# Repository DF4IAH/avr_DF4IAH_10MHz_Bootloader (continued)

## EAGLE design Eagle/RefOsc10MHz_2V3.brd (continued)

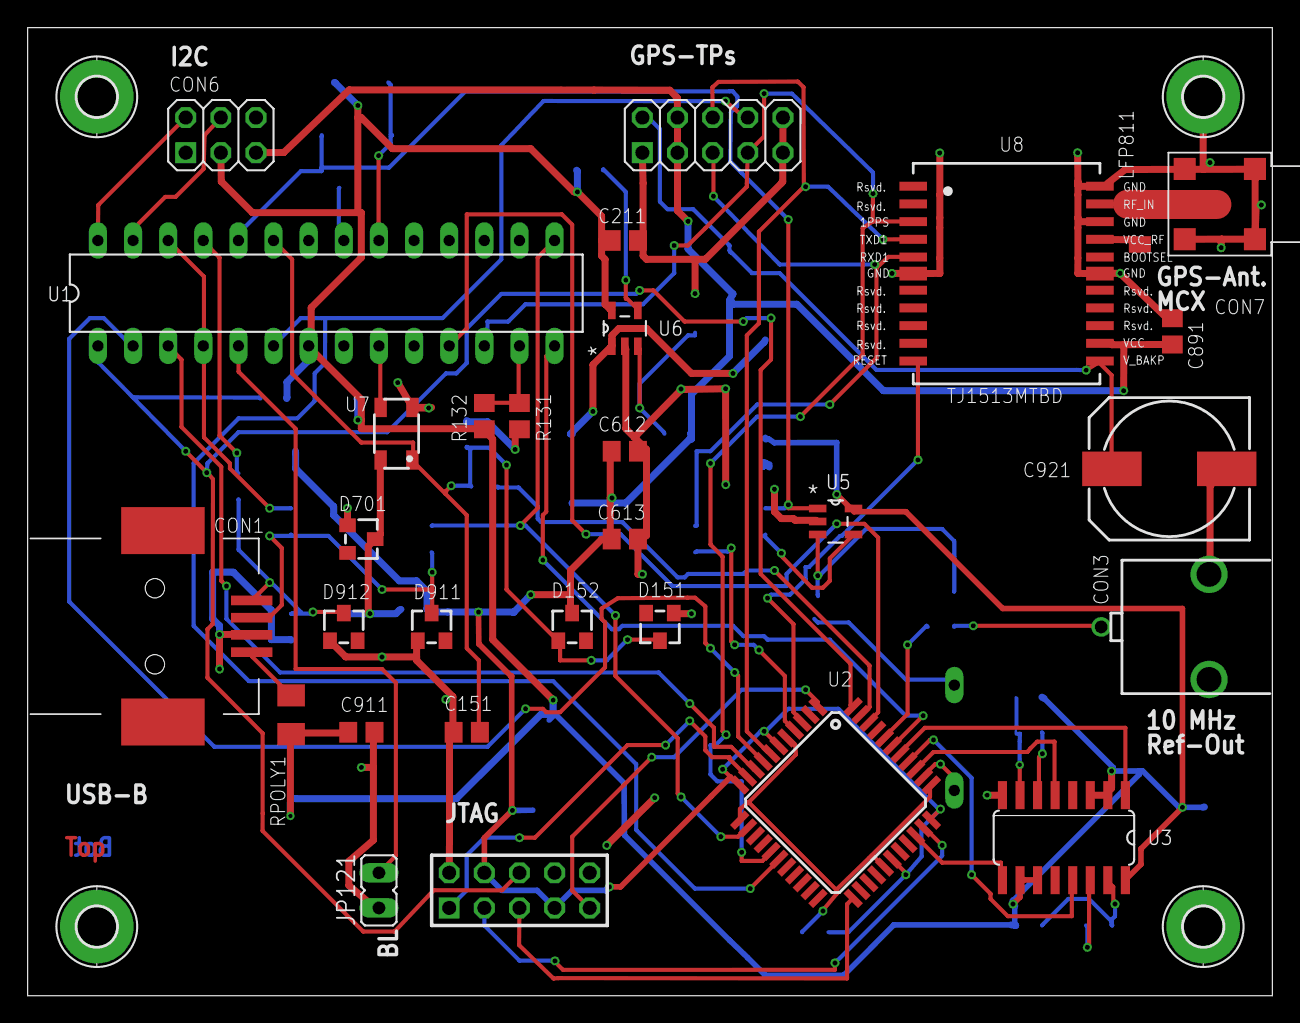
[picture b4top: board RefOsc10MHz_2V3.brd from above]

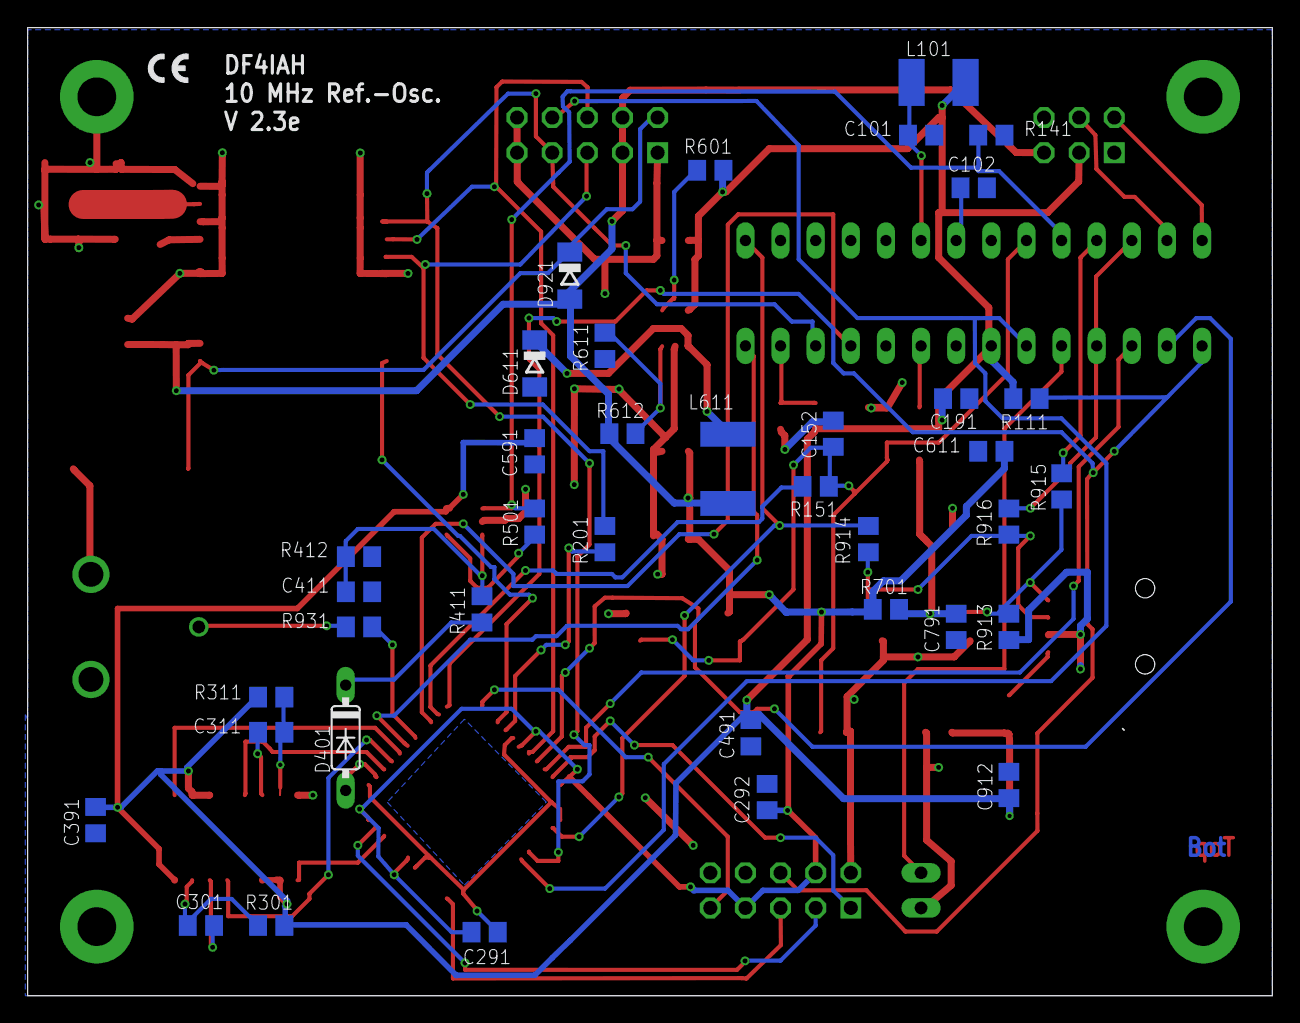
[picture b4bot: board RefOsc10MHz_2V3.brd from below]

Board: 2 copper layers, 90.0 x 70.0 mm, 72 parts (38 on the bottom side), 55 nets.

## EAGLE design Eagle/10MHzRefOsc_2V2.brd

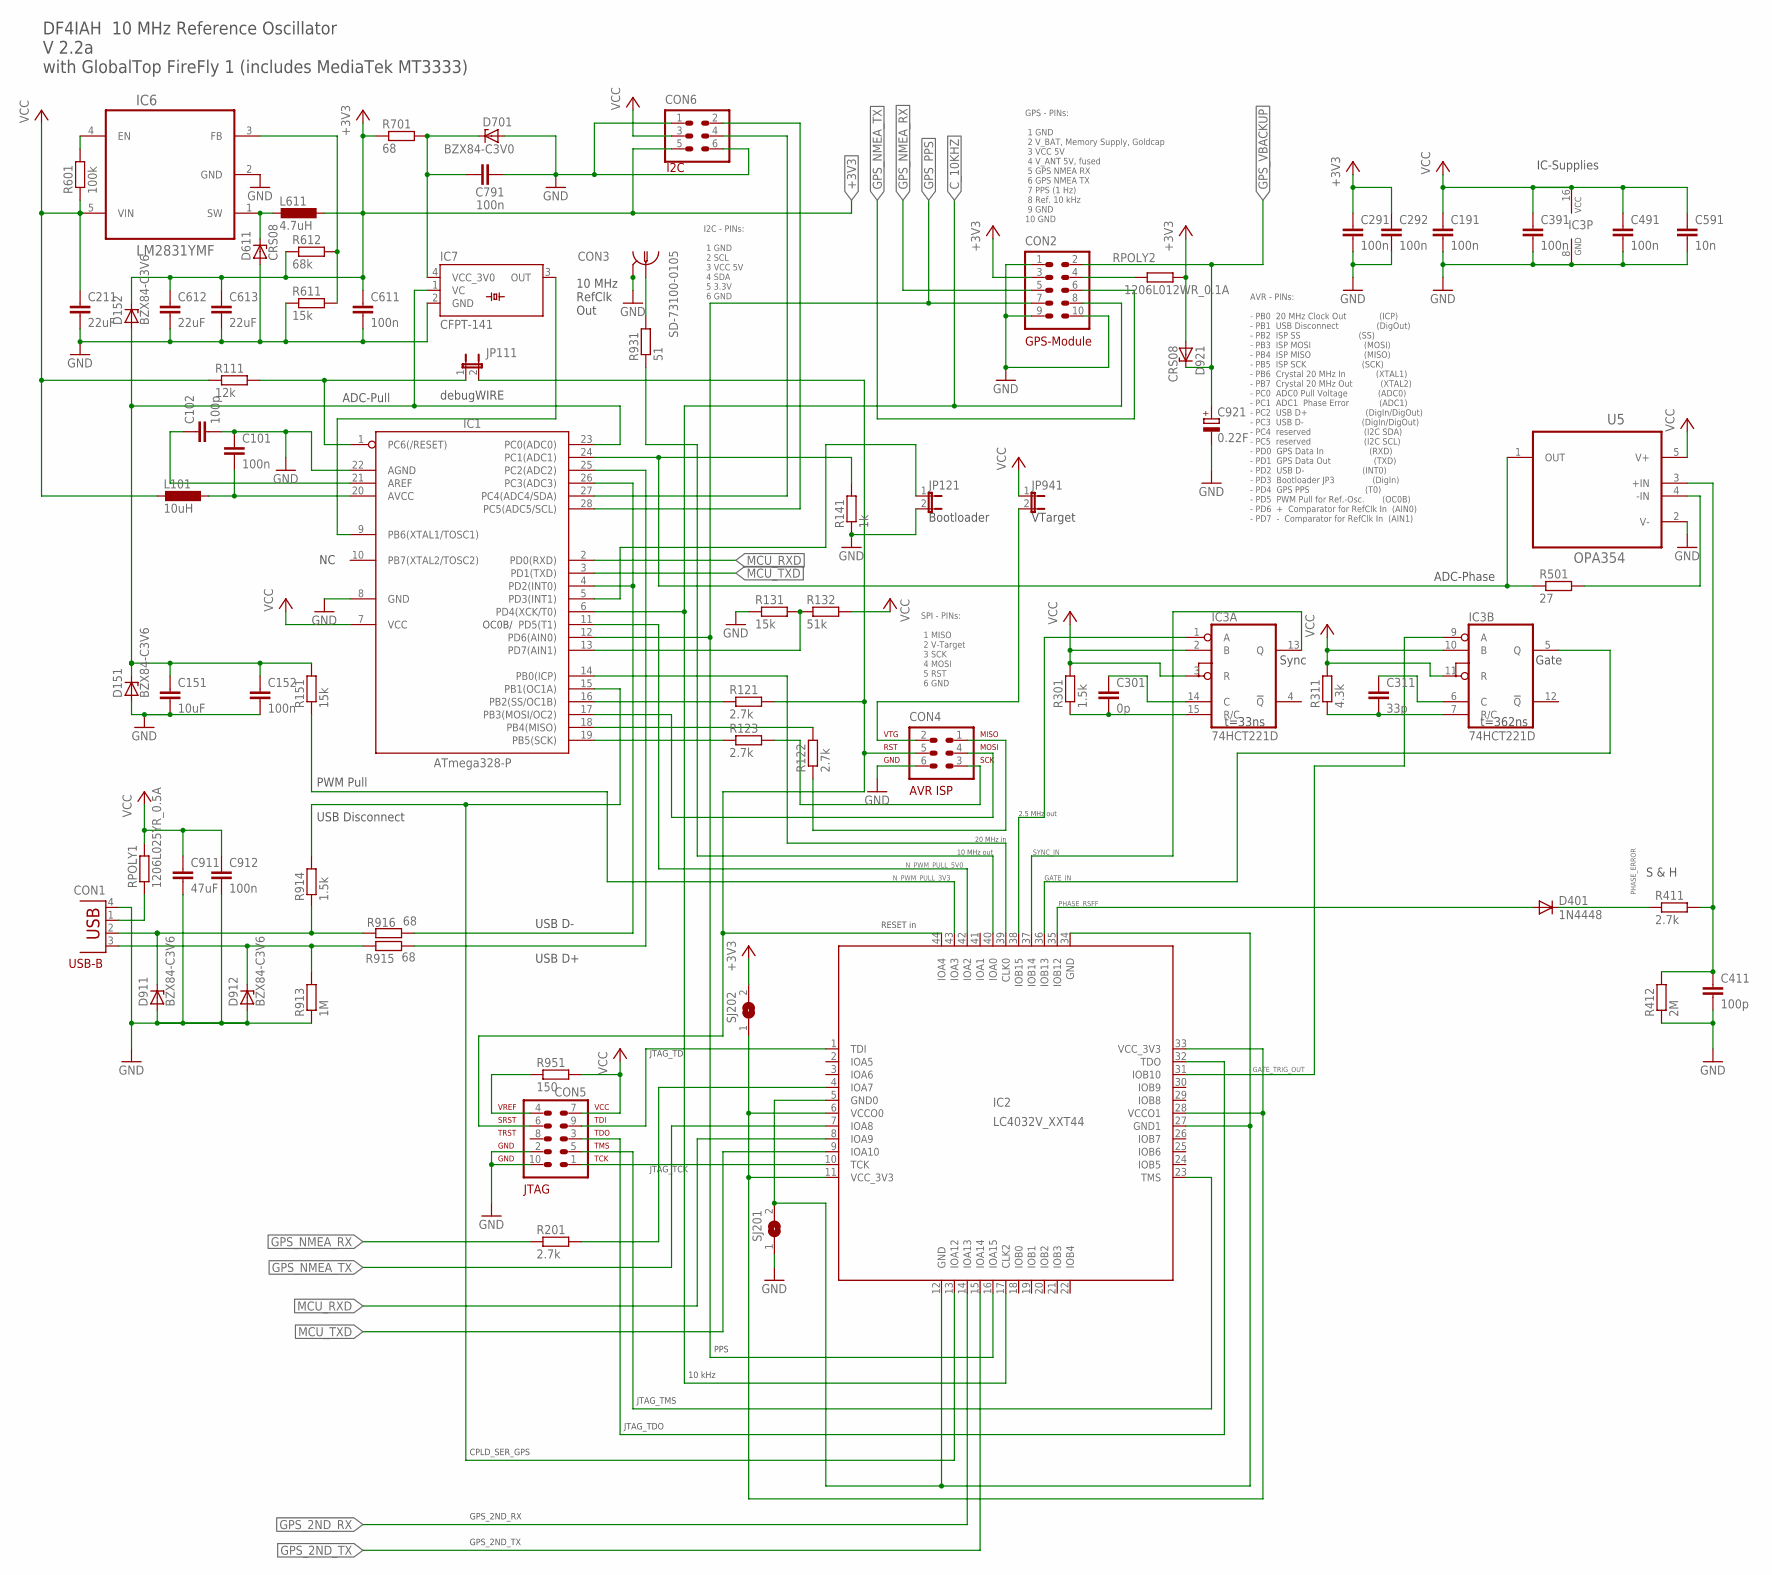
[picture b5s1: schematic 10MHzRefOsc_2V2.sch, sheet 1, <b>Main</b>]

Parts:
C101, C152, C191, C291, C292, C391, C491, C611, C791, C912: 100n; C0805
C102, C411: 100p; C0805
C151: 10uF; C0805
C211, C612, C613: 22uF; C0805
C301: 0p; C0805
C311: 33p; C0805
C591: 10n; C0805
C911: 47uF; C0805
C921: 0.22F; 140CLH-1010
CON1: TYCO-AMP_USBUSB-B_SMT; TYCO-AMP_USB-B_SMT
CON2: HEADER-2X5SMD; 2X5SMD
CON3: SD-73100-0105; MOLEX_BNC-JACK-50R_SD-73100-0105
CON4: AVR-ISP-6SMD; 2X3SMD
CON5: AVR-JTAG-10SMD; 2X5SMD
CON6: HEADER-2X3SMD; 2X03SMD
D151, D152, D911, D912: BZX84-C3V6; TO236
D401: 1N4448; SOD123
D611, D921: CRS08; SOD80C
D701: BZX84-C3V0; TO236
IC1: ATmega328-P; DIL28-3
IC2: LC4032V_XXT44; TQFP44
IC3: 74HCT221D; SO16
IC6: LM2831YMF; SOT95P280X145-5N
IC7: CFPT-141
JP111, JP121, JP941: JP1E; JP1
L101: 10uH; L1812
L611: 4.7uH; L5650M
R111: 12k; R0805
R121, R122, R123, R201, R411: 2.7k; R0805
R131, R151, R611: 15k; R0805
R132: 51k; R0805
R141: 1k; R0805
R301, R914: 1.5k; R0805
R311: 4.3k; R0805
R412: 2M; R0805
R501: 27; R0805
R601: 100k; R0805
R612: 68k; R0805
R701, R915, R916: 68; R0805
R913: 1M; R0805
R931: 51; R0805
R951: 150; R0805
RPOLY1: 1206L025YR_0.5A; M1206
RPOLY2: 1206L012WR_0.1A; M1206
SJ201, SJ202: SJ
U5: OPA354; SOT-23-5

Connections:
+3V0: C791.1, D701.C, IC7.4 (VCC_3V0), R701.2
+3V3: C291.1, C292.1, C611.1, C612.1, C613.1, CON2.3, CON6.5, D152.C, D921.A, L611.1, R612.1, R701.1, RPOLY2.2, SJ202.2
ADC_PHASE: IC1.24 (PC1(ADC1)), R141.2, R501.1, U5.1 (OUT)
ADC_PHASE_SAMPLEHOLD: C411.1, R411.2, R412.2, U5.3 (+IN)
AIN1: IC1.13 (PD7(AIN1)), R131.2, R132.1
AREF: C102.1, IC1.21 (AREF)
AVCC: C101.2, IC1.20 (AVCC), L101.1
CPLD_GPS_NMEA_RX: IC2.4 (IOA7), R201.2
C_2MHZ5: IC2.38 (IOB15), IC3.1 (A)
C_10KHZ: CON2.8, IC1.6 (PD4(XCK/T0)), IC2.17 (CLK2)
C_10MHZ: IC2.40 (IOA0), R931.1
C_20MHZ: IC1.14 (PB0(ICP)), IC2.39 (CLK0)
EN: IC6.4 (EN), R601.2
FB: IC6.3 (FB), R611.2, R612.2
GATE_IN: IC2.36 (IOB13), IC3.5 (Q)
GATE_TRIG_OUT: IC2.31 (IOB10), IC3.9 (A)
GND: C101.1, C102.2, C151.2, C152.2, C191.2, C211.2, C291.2, C292.2, C391.2, C411.2, C491.2, C591.2, C611.2, C612.2, C613.2, C791.2, C911.2, C912.2, C921.-, CON1.4 (GND), CON2.1, CON2.9, CON2.10, CON3.2, CON3.3, CON4.6, CON5.2, CON5.10, CON6.1, CON6.6, D151.A, D611.A, D701.A, D911.A, D912.A, IC1.8 (GND), IC1.22 (AGND), IC3.8 (GND), IC6.2 (GND), IC7.2 (GND), JP121.2, R131.1, R141.1, R412.1, R611.1, R913.1, SJ201.1, U5.2 (V-); also elsewhere on the board
GND_SJ1: IC2.5 (GND0), IC2.12 (GND), IC2.27 (GND1), IC2.34 (GND), SJ201.2
GPS_2ND_RX: IC2.14 (IOA13); also elsewhere on the board
GPS_2ND_TX: IC2.15 (IOA14); also elsewhere on the board
GPS_ANT_PWR: CON2.4, RPOLY2.1; also elsewhere on the board
GPS_NMEA_RX: CON2.5, R201.1; also elsewhere on the board
GPS_NMEA_TX: CON2.6, IC2.7 (IOA8); also elsewhere on the board
GPS_PPS: CON2.7, IC1.12 (PD6(AIN0)), IC2.16 (IOA15); also elsewhere on the board
GPS_VBACKUP: C921.+, CON2.2, D921.C; also elsewhere on the board
INT1: IC1.5 (PD3(INT1)), JP121.1
ISP_MISO: CON4.1, R122.1
ISP_MOSI: CON4.4, IC1.17 (PB3(MOSI/OC2))
ISP_SCK: CON4.3, R123.2
ISP_VTARGET: CON4.2, JP941.2
JTAG_SRST: CON4.5, CON5.6, IC2.44 (IOA4), JP111.2, R121.2
JTAG_TCK: CON5.1, IC2.10 (TCK)
JTAG_TDI: CON5.9, IC2.1 (TDI)
JTAG_TDO: CON5.3, IC2.32 (TDO)
JTAG_TMS: CON5.5, IC2.23 (TMS)
JTAG_VREF: CON5.4, R951.1
MCU_RXD: IC1.2 (PD0(RXD)), IC2.8 (IOA9)
MCU_TXD: IC1.3 (PD1(TXD)), IC2.9 (IOA10)
MISO: IC1.18 (PB4(MISO)), R122.2
unnamed: CON6.2, IC1.28 (PC5(ADC5/SCL))
unnamed: CON6.4, IC1.27 (PC4(ADC4/SDA))
unnamed: CON3.1, R931.2
unnamed: C311.2, IC3.7 (R/C), R311.1
unnamed: C311.1, IC3.6 (C)
unnamed: C301.2, IC3.15 (R/C), R301.1
unnamed: C301.1, IC3.14 (C)
N_ADC_PULL: C151.1, C152.1, D151.C, D152.A, IC1.23 (PC0(ADC0)), IC7.1 (VC), R151.2
N_PWM_PULL_3V3: IC2.43 (IOA3), R151.1
N_PWM_PULL_5V0: IC1.11 (PD5(T1)), IC2.42 (IOA2)
N_USB_DISC: IC1.15 (PB1(OC1A)), IC2.13 (IOA12), R914.2
N_USB_DMNS: IC1.4 (PD2(INT0)), IC1.26 (PC3(ADC3)), R916.2
N_USB_DPLS: IC1.25 (PC2(ADC2)), R915.2
PHASE_ERROR: D401.C, R411.1
PHASE_RSFF: D401.A, IC2.35 (IOB12)
RESET: IC1.1 (PC6(/RESET)), JP111.1, R111.2
SCK: IC1.19 (PB5(SCK)), R123.1
SS: IC1.16 (PB2(SS/OC1B)), R121.1
SW: D611.C, IC6.1 (SW), L611.2
SYNC_IN: IC2.37 (IOB14), IC3.13 (Q)
TOSC1: IC1.9 (PB6(XTAL1/TOSC1)), IC7.3 (OUT)
U5_FB: R501.2, U5.4 (-IN)
USB_D_MIN: CON1.2 (D-), D911.C, R914.1, R916.1
USB_D_PLS: CON1.3 (D+), D912.C, R913.2, R915.1
USB_PWR: CON1.1 (VBUS), RPOLY1.1
VCC: C191.1, C211.1, C391.1, C491.1, C591.1, C911.1, C912.1, CON5.7, CON6.3, IC1.7 (VCC), IC3.2 (B), IC3.3 (R), IC3.10 (B), IC3.11 (R), IC3.16 (VCC), IC6.5 (VIN), JP941.1, L101.2, R111.1, R132.2, R301.2, R311.2, R601.1, R951.2, RPOLY1.2, U5.5 (V+)
VCC_3V3_SJ2: IC2.6 (VCCO0), IC2.11 (VCC_3V3), IC2.28 (VCCO1), IC2.33 (VCC_3V3), SJ202.1

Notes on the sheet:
VTarget
debugWIRE
USB-B
AVR - PINs: - PB0 20 MHz Clock Out (ICP) - PB1 USB Disconnect (DigOut) - PB2 ISP SS (SS) - PB3 ISP MOSI (MOSI) - PB4 ISP MISO (MISO) - PB5 ISP SCK (SCK) - PB6 Crystal 20 MHz In (XTAL1) - PB7 Crystal 20 MHz Out (XTAL2) - PC0 ADC0 Pull Voltage (ADC0) - PC1 ADC1 Phase Error (ADC1) - PC2 USB D+ (DigIn/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
10 MHz RefClk Out
Bootloader
Gate
GPS-Module
GPS - PINs: 1 GND 2 V_BAT, Memory Supply, Goldcap 3 VCC 5V 4 V_ANT 5V, fused 5 GPS NMEA RX 6 GPS NMEA TX 7 PPS (1 Hz) 8 Ref. 10 kHz 9 GND 10 GND
S & H
ADC-Phase
PWM Pull
ADC-Pull
Sync
t=33ns
t=362ns
IC-Supplies
20 MHz in
10 MHz out
2.5 MHz out
DF4IAH 10 MHz Reference Oscillator V 2.2a with GlobalTop FireFly 1 (includes MediaTek MT3333)
USB Disconnect
USB D-
USB D+
SPI - PINs: 1 MISO 2 V-Target 3 SCK 4 MOSI 5 RST 6 GND
10 kHz
PPS
RESET in
JTAG_TMS
JTAG_TDO
JTAG_TCK
JTAG_TDI
CPLD_SER_GPS
I2C - PINs: 1 GND 2 SCL 3 VCC 5V 4 SDA 5 3.3V 6 GND
I2C
OC0B/
GPS_2ND_RX
GPS_2ND_TX

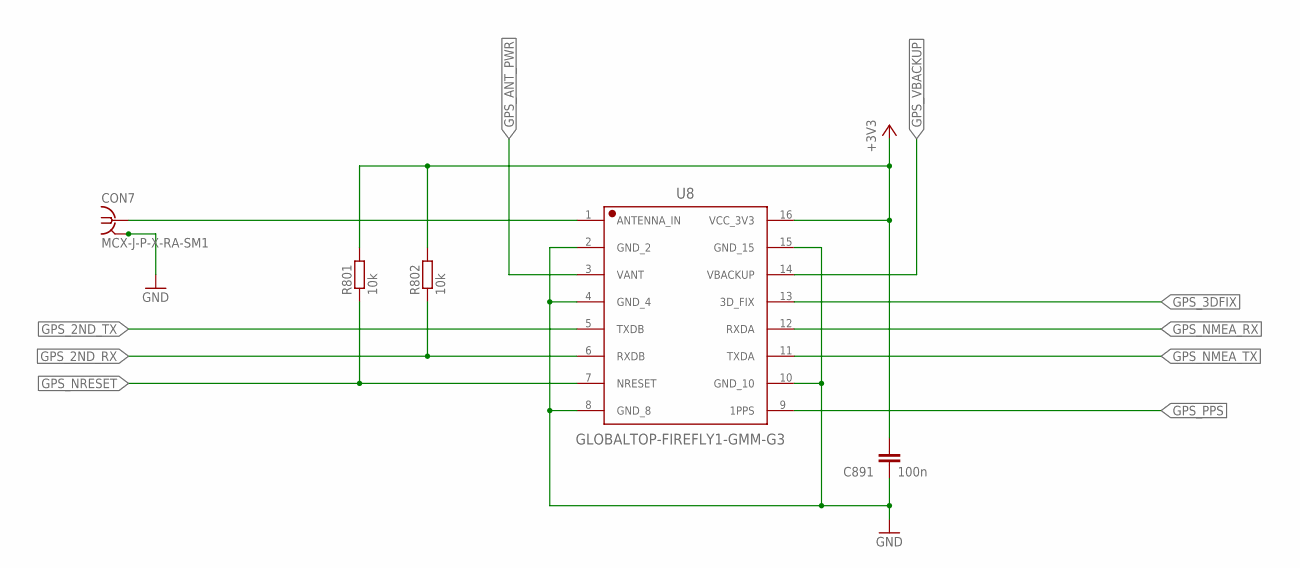
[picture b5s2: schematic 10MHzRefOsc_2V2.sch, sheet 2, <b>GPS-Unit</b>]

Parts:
C891: 100n; C0805
CON7: MCX-J-P-X-RA-SM1
R801, R802: 10k; R0805
U8: GLOBALTOP-FIREFLY1-GMM-G3

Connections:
GND: C891.2, CON7.2, CON7.3, CON7.4, CON7.5, U8.2 (GND_2), U8.4 (GND_4), U8.8 (GND_8), U8.10 (GND_10), U8.15 (GND_15); also elsewhere on the board
GPS_2ND_RX: R802.1, U8.6 (RXDB); also elsewhere on the board
GPS_2ND_TX: U8.5 (TXDB); also elsewhere on the board
GPS_3DFIX: U8.13 (3D_FIX)
GPS_ANT_PWR: U8.3 (VANT); also elsewhere on the board
GPS_NMEA_RX: U8.12 (RXDA); also elsewhere on the board
GPS_NMEA_TX: U8.11 (TXDA); also elsewhere on the board
GPS_NRESET: R801.1, U8.7 (NRESET)
GPS_PPS: U8.9 (1PPS); also elsewhere on the board
GPS_VBACKUP: U8.14 (VBACKUP); also elsewhere on the board
unnamed: CON7.1, U8.1 (ANTENNA_IN)
VCC_3V3: C891.1, R801.2, R802.2, U8.16 (VCC_3V3)

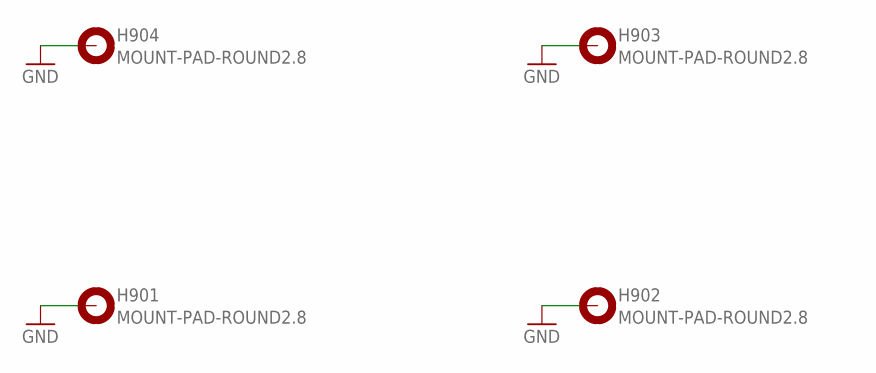
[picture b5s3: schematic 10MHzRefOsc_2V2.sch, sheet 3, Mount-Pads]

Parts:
H901, H902, H903, H904: MOUNT-PAD-ROUND2.8; 2,8-PAD

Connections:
GND: H901.B2,8, H902.B2,8, H903.B2,8, H904.B2,8; also elsewhere on the board

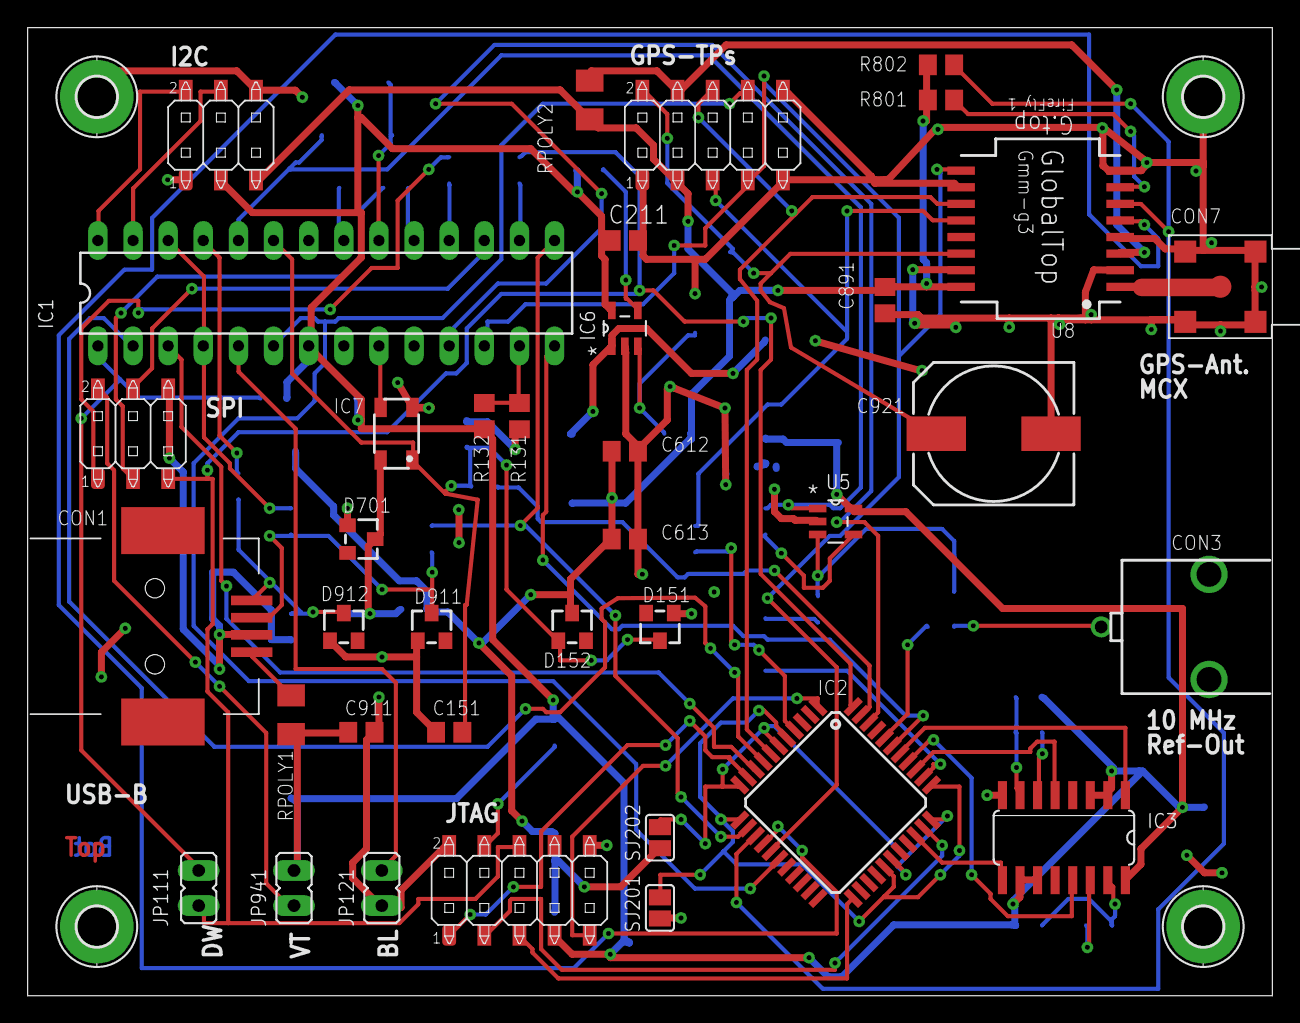
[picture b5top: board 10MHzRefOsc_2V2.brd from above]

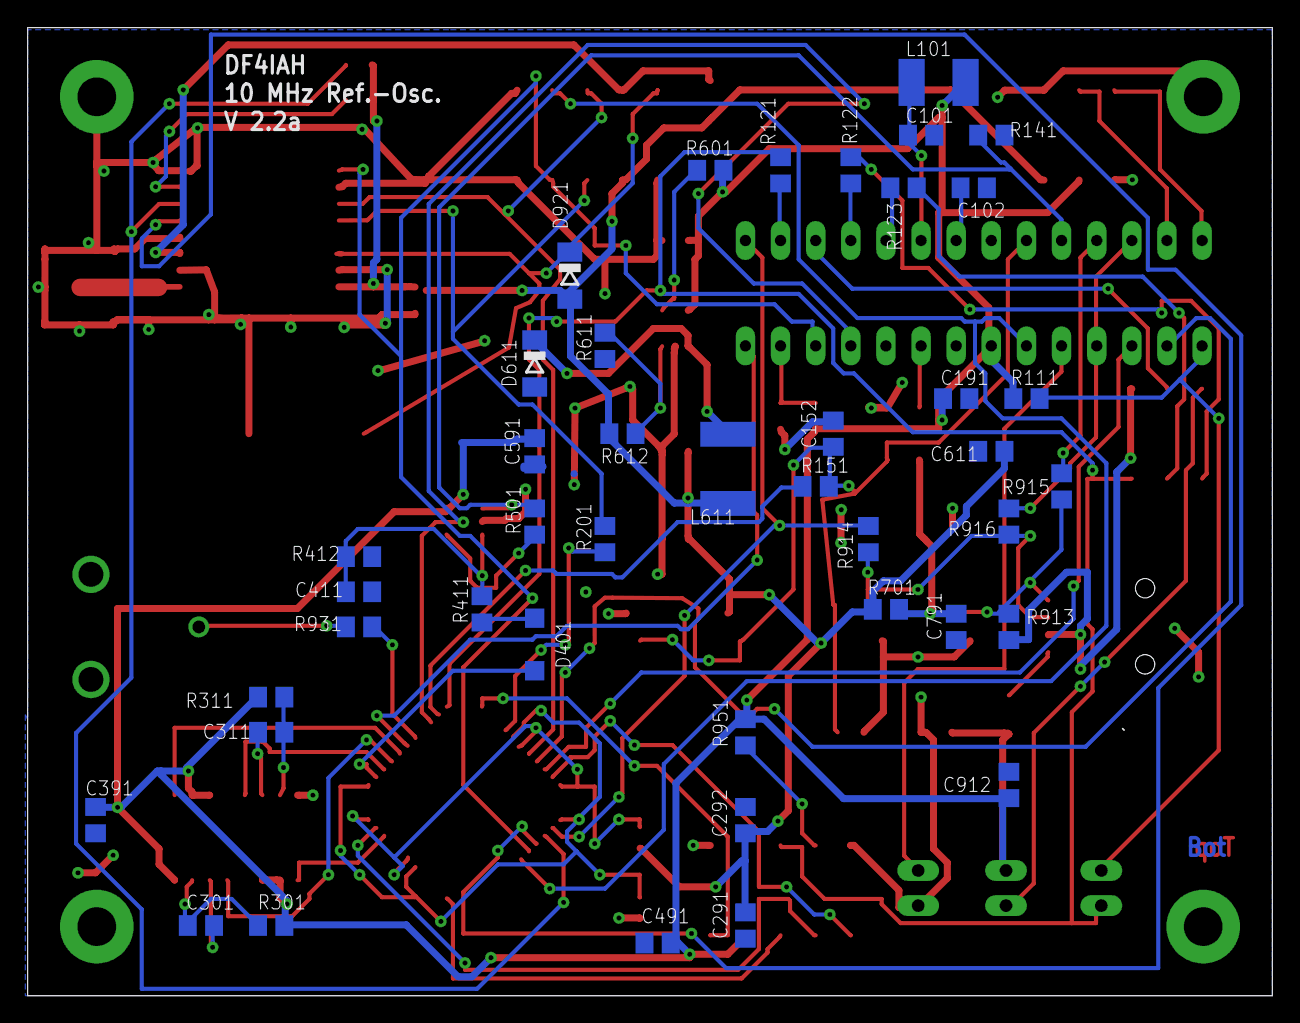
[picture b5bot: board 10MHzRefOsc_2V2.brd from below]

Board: 2 copper layers, 90.0 x 70.0 mm, 83 parts (42 on the bottom side), 69 nets.

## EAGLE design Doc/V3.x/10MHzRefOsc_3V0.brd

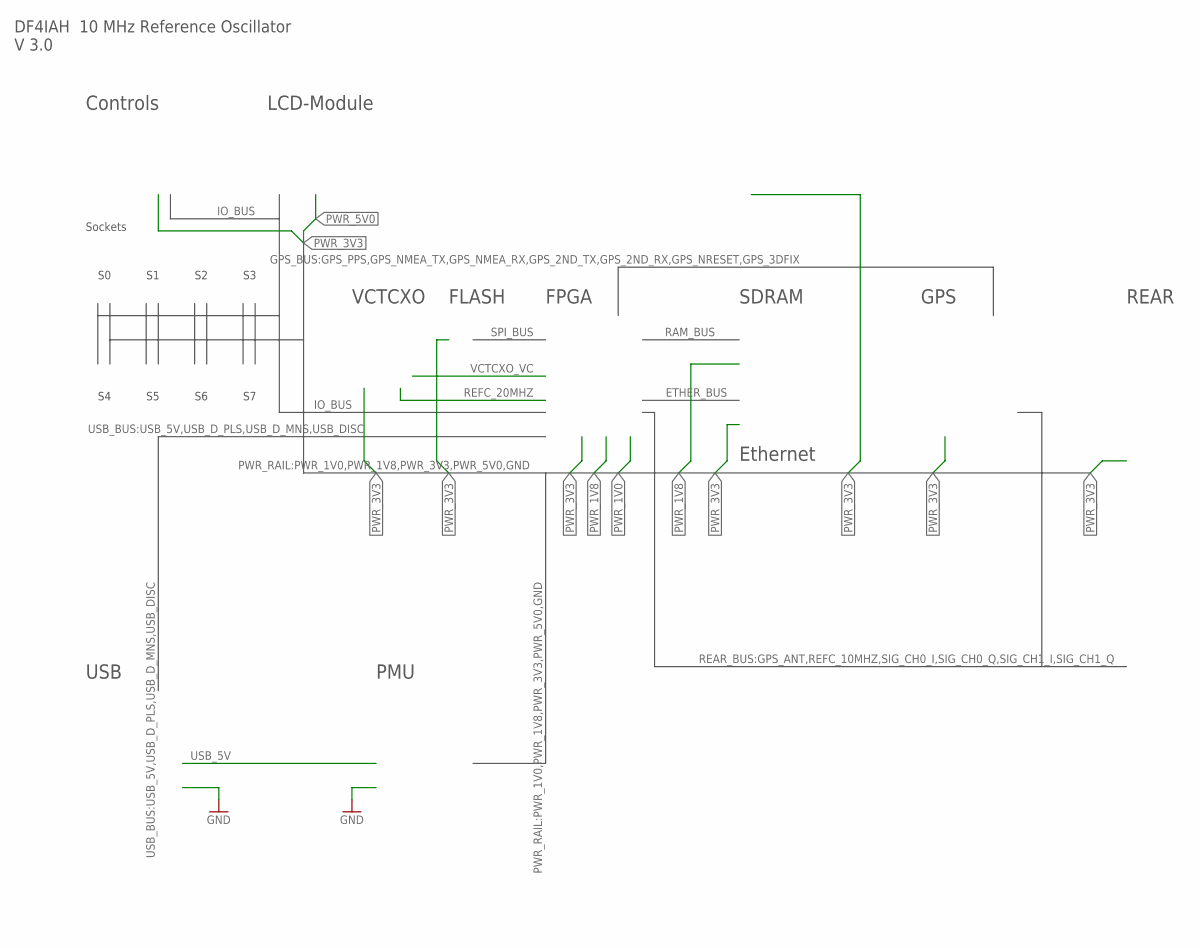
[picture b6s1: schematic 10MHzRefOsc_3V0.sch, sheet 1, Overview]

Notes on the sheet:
VCTCXO
FPGA
GPS
REAR
LCD-Module
Controls
USB
PMU
Sockets
SDRAM
Ethernet
FLASH
DF4IAH 10 MHz Reference Oscillator V 3.0

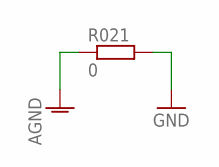
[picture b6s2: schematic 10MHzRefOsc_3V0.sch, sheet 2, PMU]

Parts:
R021: 0; R0805

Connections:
AGND: R021.1; also elsewhere on the board
GND: R021.2; also elsewhere on the board

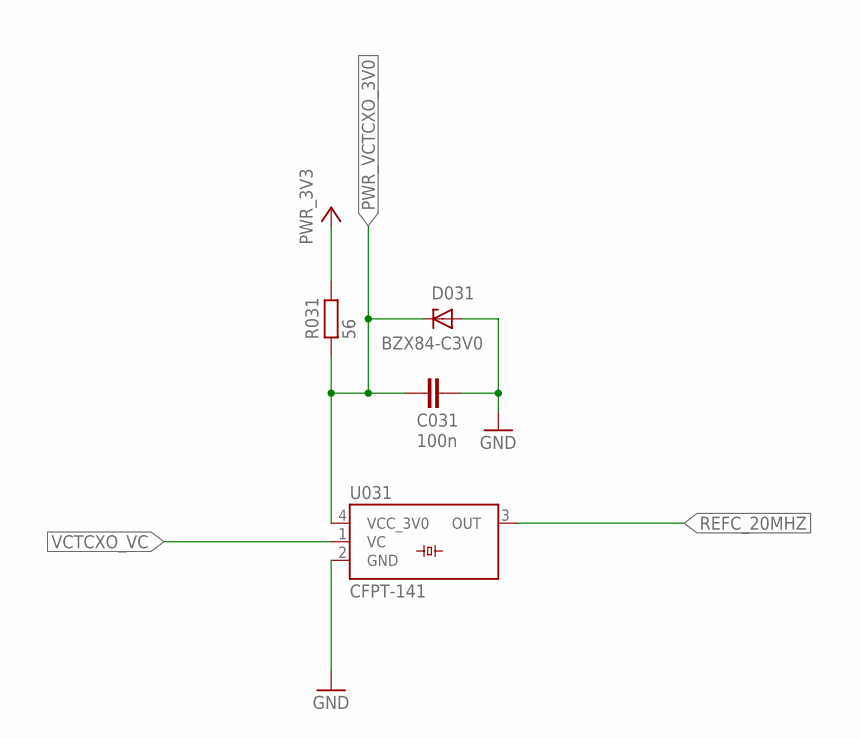
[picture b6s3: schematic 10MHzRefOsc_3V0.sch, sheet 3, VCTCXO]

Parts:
C031: 100n; C0805
D031: BZX84-C3V0; TO236
R031: 56; R0805
U031: CFPT-141

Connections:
GND: C031.2, D031.A, U031.2 (GND); also elsewhere on the board
PWR_3V3: R031.1; also elsewhere on the board
PWR_VCTCXO_3V0: C031.1, D031.C, R031.2, U031.4 (VCC_3V0)
REFC_20MHZ: U031.3 (OUT)
VCTCXO_VC: U031.1 (VC)

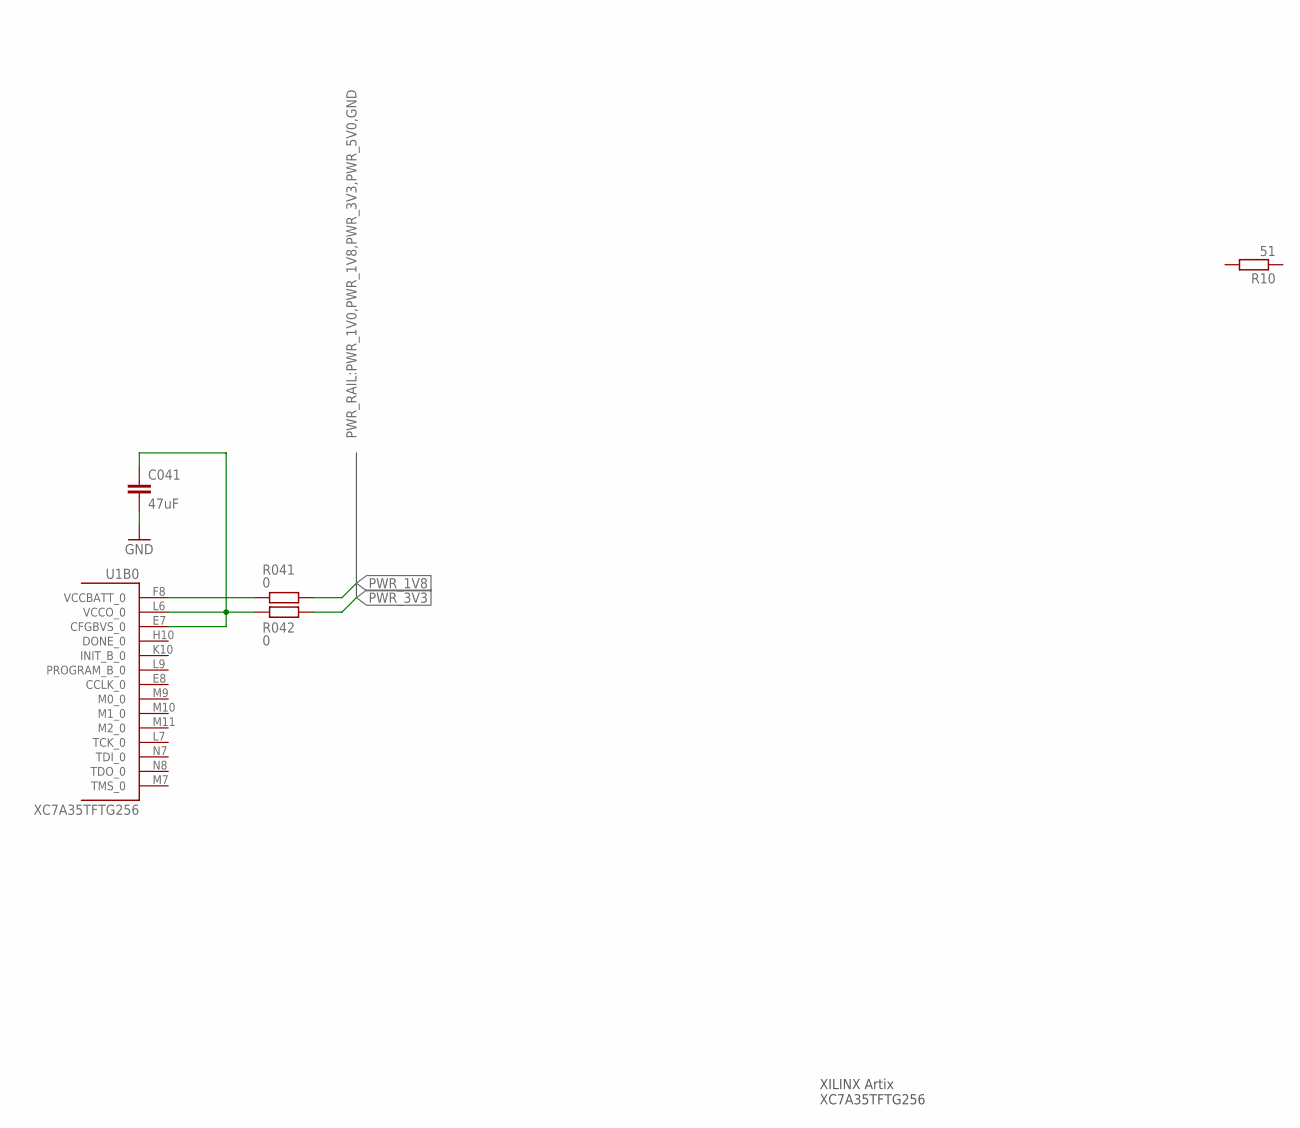
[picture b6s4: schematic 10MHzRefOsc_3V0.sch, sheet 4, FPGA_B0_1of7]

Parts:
C041: 47uF; C0805
R10: 51; R0805
R041, R042: 0; R0402
U1: XC7A35TFTG256; FTG256_0MM4

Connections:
FPGA_VCCBATT: R041.1, U1.F8 (VCCBATT_0)
FPGA_VCCO_0: C041.1, R042.1, U1.E7 (CFGBVS_0), U1.L6 (VCCO_0)
GND: C041.2; also elsewhere on the board
PWR_1V8: R041.2; also elsewhere on the board
PWR_3V3: R042.2; also elsewhere on the board

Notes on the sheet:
XILINX Artix XC7A35TFTG256

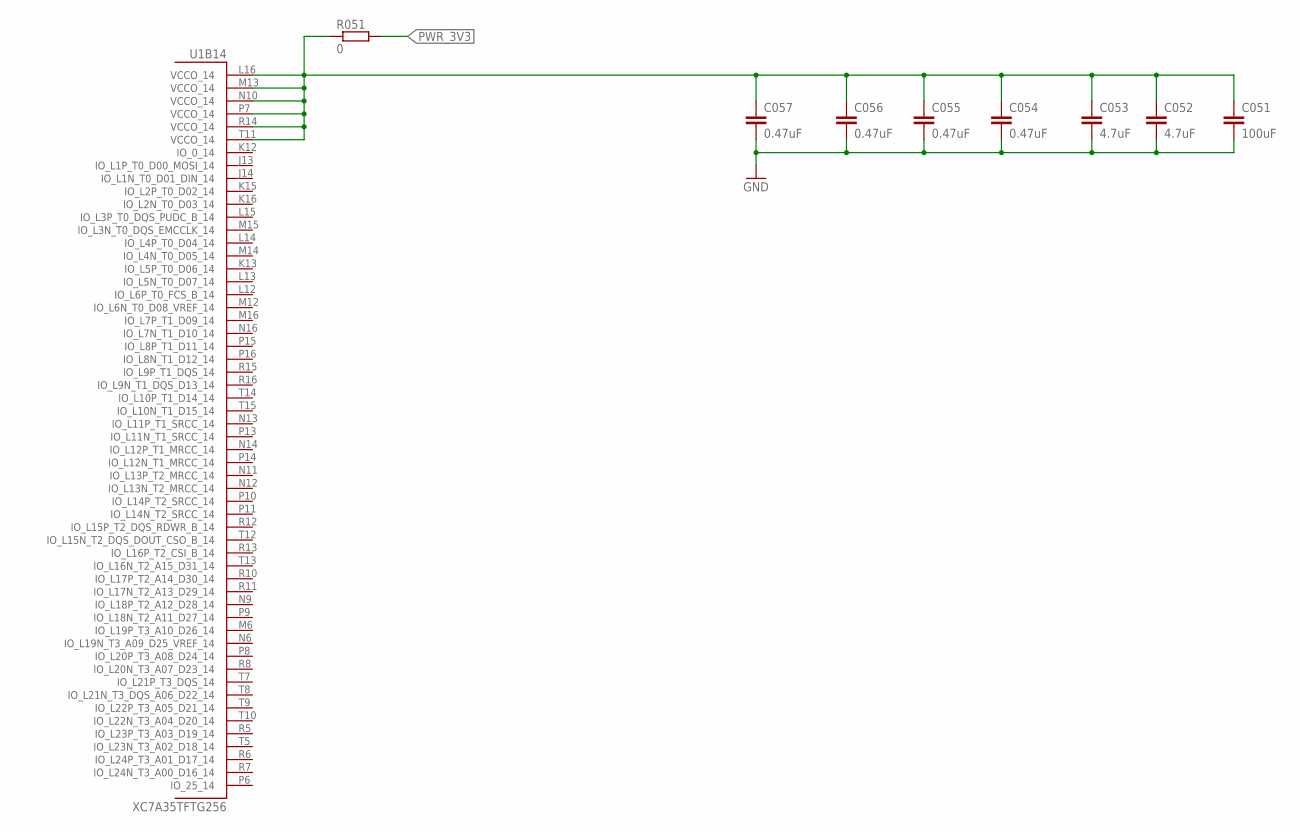
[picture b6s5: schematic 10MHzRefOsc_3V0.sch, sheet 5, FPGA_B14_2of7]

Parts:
C051: 100uF; C1206
C052, C053: 4.7uF; C0402
C054, C055, C056, C057: 0.47uF; C0402
R051: 0; R0402
U1: XC7A35TFTG256; FTG256_0MM4

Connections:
FPGA_VCCO_14: C051.1, C052.1, C053.1, C054.1, C055.1, C056.1, C057.1, R051.1, U1.L16 (VCCO_14), U1.M13 (VCCO_14), U1.N10 (VCCO_14), U1.P7 (VCCO_14), U1.R14 (VCCO_14), U1.T11 (VCCO_14)
GND: C051.2, C052.2, C053.2, C054.2, C055.2, C056.2, C057.2; also elsewhere on the board
PWR_3V3: R051.2; also elsewhere on the board

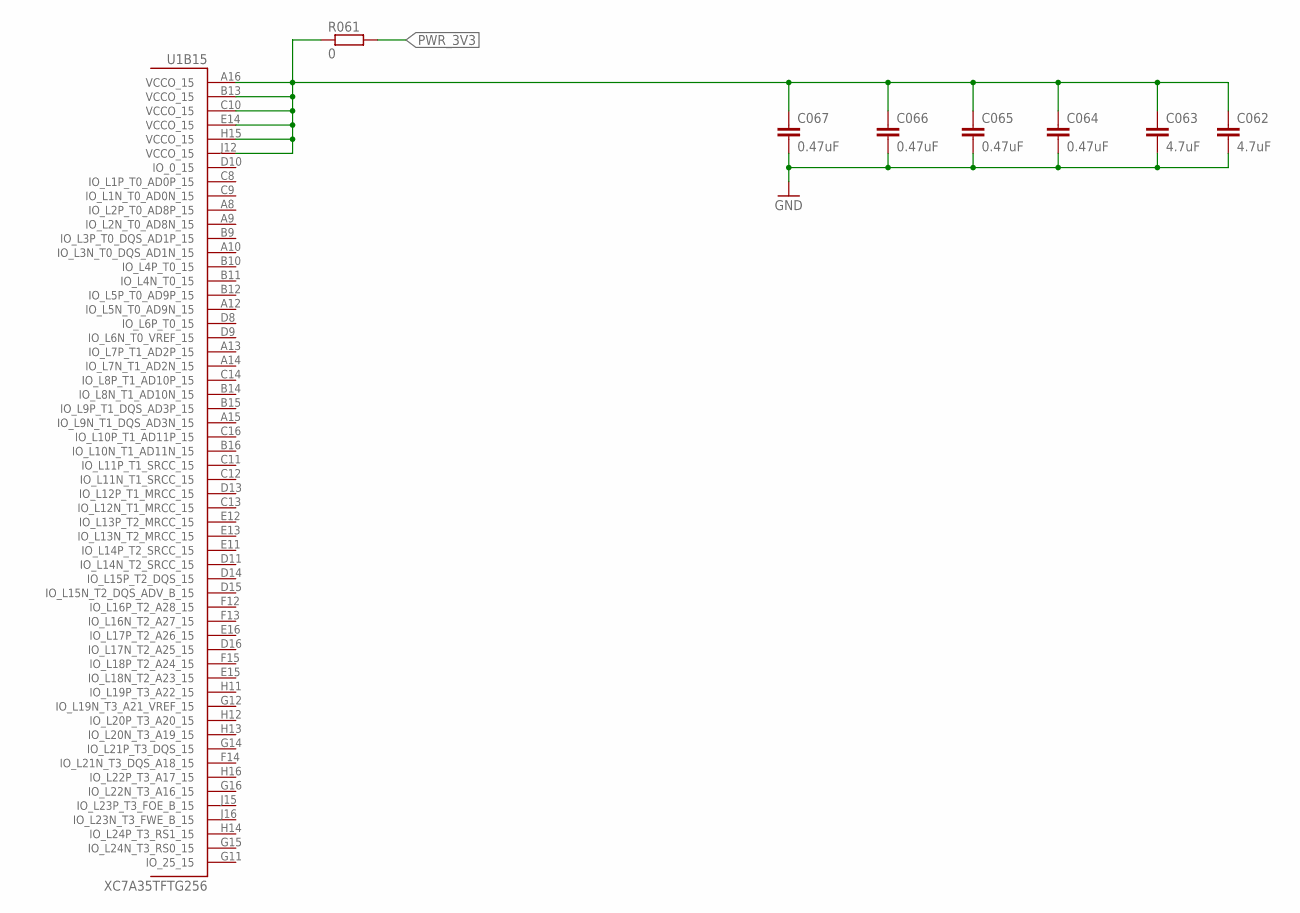
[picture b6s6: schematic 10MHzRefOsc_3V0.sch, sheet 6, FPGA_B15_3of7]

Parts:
C062, C063: 4.7uF; C0402
C064, C065, C066, C067: 0.47uF; C0402
R061: 0; R0402
U1: XC7A35TFTG256; FTG256_0MM4

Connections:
FPGA_VCCO_15: C062.1, C063.1, C064.1, C065.1, C066.1, C067.1, R061.1, U1.A16 (VCCO_15), U1.B13 (VCCO_15), U1.C10 (VCCO_15), U1.E14 (VCCO_15), U1.H15 (VCCO_15), U1.J12 (VCCO_15)
GND: C062.2, C063.2, C064.2, C065.2, C066.2, C067.2; also elsewhere on the board
PWR_3V3: R061.2; also elsewhere on the board

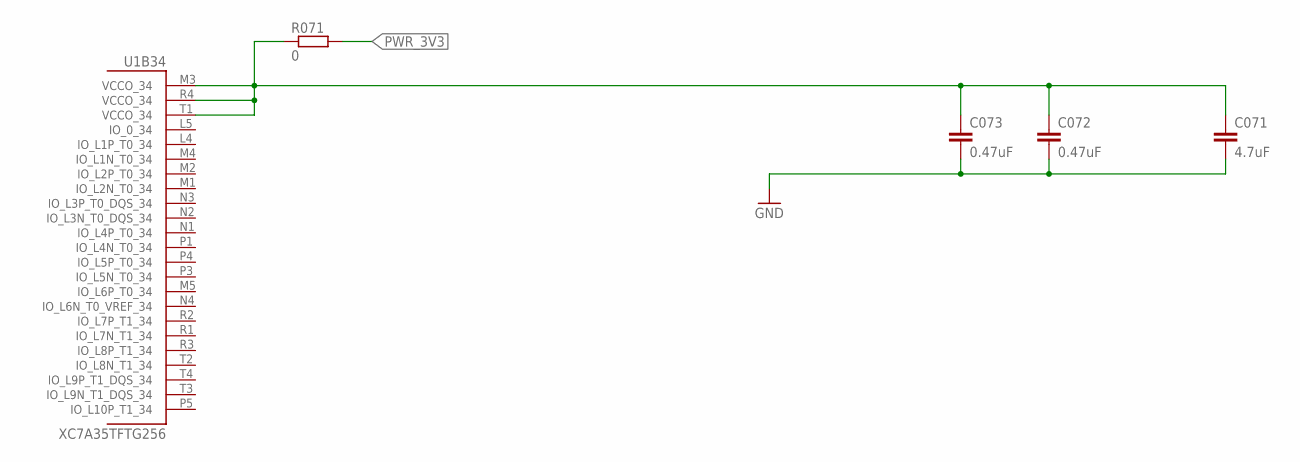
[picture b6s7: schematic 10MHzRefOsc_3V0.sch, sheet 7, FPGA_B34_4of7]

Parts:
C071: 4.7uF; C0402
C072, C073: 0.47uF; C0402
R071: 0; R0402
U1: XC7A35TFTG256; FTG256_0MM4

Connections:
FPGA_VCCO_34: C071.1, C072.1, C073.1, R071.1, U1.M3 (VCCO_34), U1.R4 (VCCO_34), U1.T1 (VCCO_34)
GND: C071.2, C072.2, C073.2; also elsewhere on the board
PWR_3V3: R071.2; also elsewhere on the board

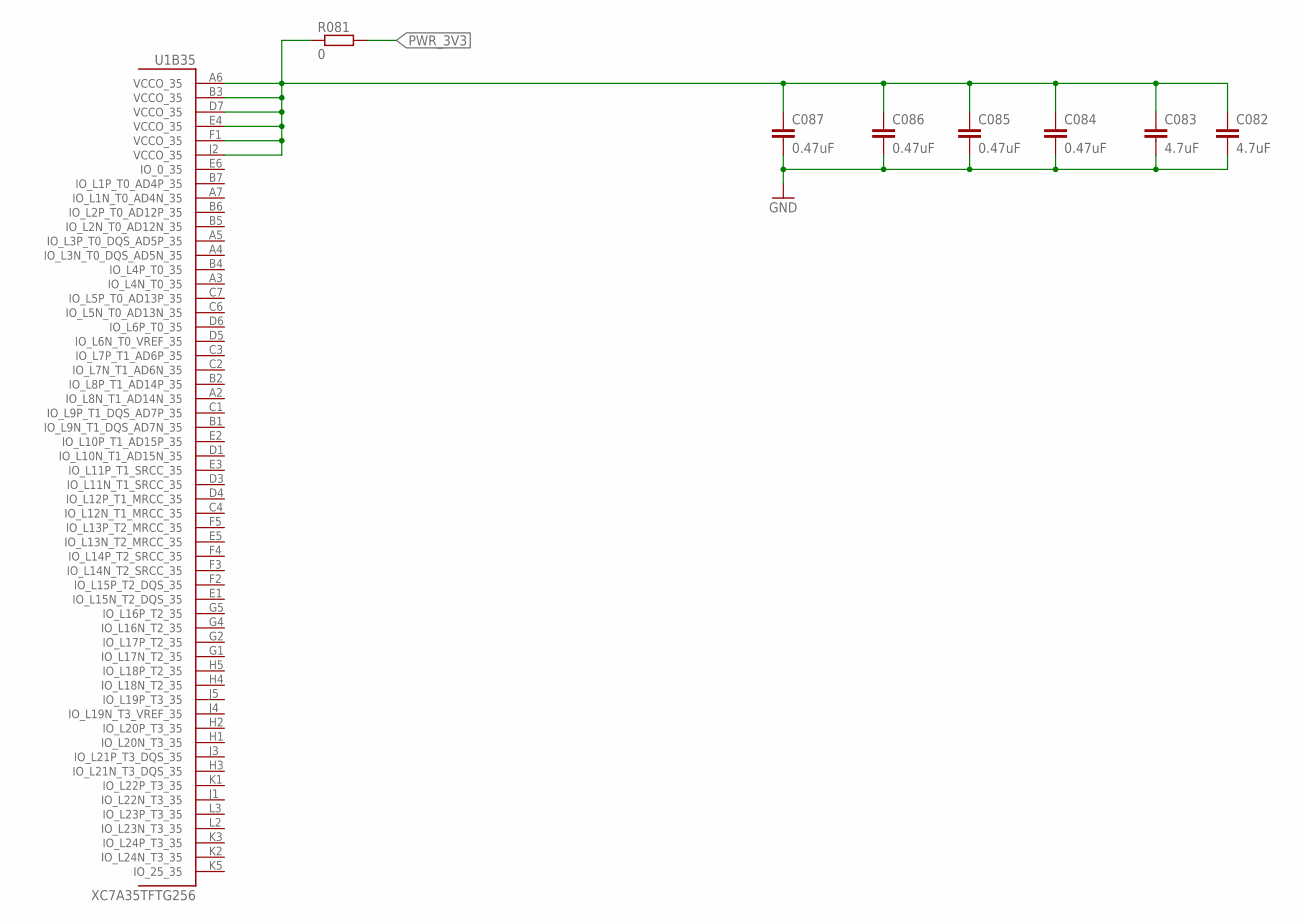
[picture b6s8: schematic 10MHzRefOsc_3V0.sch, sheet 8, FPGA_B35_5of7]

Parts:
C082, C083: 4.7uF; C0402
C084, C085, C086, C087: 0.47uF; C0402
R081: 0; R0402
U1: XC7A35TFTG256; FTG256_0MM4

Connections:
FPGA_VCCO_35: C082.1, C083.1, C084.1, C085.1, C086.1, C087.1, R081.1, U1.A6 (VCCO_35), U1.B3 (VCCO_35), U1.D7 (VCCO_35), U1.E4 (VCCO_35), U1.F1 (VCCO_35), U1.J2 (VCCO_35)
GND: C082.2, C083.2, C084.2, C085.2, C086.2, C087.2; also elsewhere on the board
PWR_3V3: R081.2; also elsewhere on the board

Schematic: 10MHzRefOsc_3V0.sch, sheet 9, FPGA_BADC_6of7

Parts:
C091: 4.7uF; C0402
C092: 0.47uF; C0402
R091: 0; R0402
U1: XC7A35TFTG256; FTG256_0MM4

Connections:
AGND: U1.G7 (GNDADC_0), U1.H7 (VREFN_0), U1.J7 (VN_0); also elsewhere on the board
FPGA_ADC_VP_0: U1.H8 (VP_0)
FPGA_VCCADC_0: C091.1, C092.1, R091.1, U1.G8 (VCCADC_0)
GND: C091.2, C092.2; also elsewhere on the board
PWR_1V8: R091.2; also elsewhere on the board
PWR_1V25_PREC: U1.J8 (VREFP_0)
